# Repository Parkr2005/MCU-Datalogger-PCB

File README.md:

# MCU Data Logger PCB

A 4-layer PCB designed in KiCad for an ATmega328P-AU based microcontroller data logger. The board integrates a DS1337 real-time clock, dual 24LC1025 EEPROMs, ICSP programming interface, UART, I²C, and GPIO expansion headers.

## Features

- ATmega328P-AU Microcontroller
- DS1337 Real-Time Clock (RTC)
- Dual 24LC1025 EEPROMs
- 16 MHz System Crystal
- 32.768 kHz RTC Crystal
- ICSP Programming Header
- UART Header
- I²C Expansion Header
- GPIO Expansion Header
- Battery Input Header
- Status LEDs
- Four Mounting Holes
- Custom PCB Artwork

## PCB Specifications

| Parameter | Value |
|----------|-------|
| PCB CAD | KiCad |
| PCB Layers | 4 |
| MCU | ATmega328P-AU |
| RTC | DS1337 |
| EEPROM | 2 × 24LC1025 |
| Crystal | 16 MHz |
| RTC Crystal | 32.768 kHz |

## Project Structure

```text
├── README.md
├── .gitignore
├── MCU-Datalogger.kicad_pro
├── MCU-Datalogger.kicad_sch
└── MCU-Datalogger.kicad_pcb
```

## Verification

- ✅ Electrical Rules Check (ERC) Passed
- ✅ Design Rules Check (DRC) Passed
- ✅ Fully Routed PCB
- ✅ 3D PCB Model Generated

## Software Used

- KiCad

## Author

**Parthiv K R**

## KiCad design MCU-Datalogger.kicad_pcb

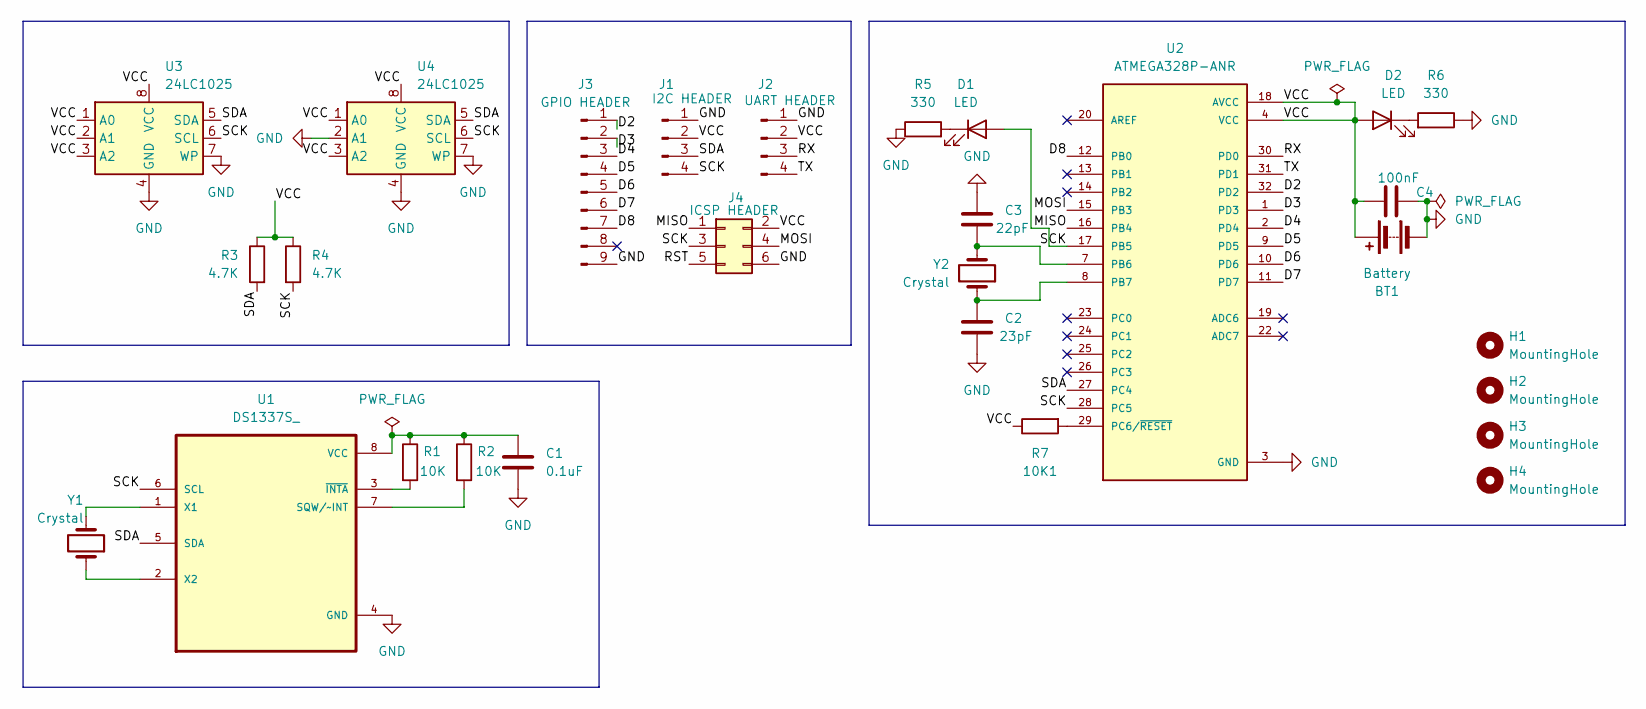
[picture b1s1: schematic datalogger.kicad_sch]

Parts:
10K1: R7; R_0805_2012Metric_Pad1.20x1.40mm_HandSolder
BT1: Battery; PinHeader_1x02_P2.54mm_Vertical
C1: 0.1uF; C_0805_2012Metric_Pad1.18x1.45mm_HandSolder
C2: 23pF; C_0805_2012Metric_Pad1.18x1.45mm_HandSolder
C3: 22pF; C_0805_2012Metric_Pad1.18x1.45mm_HandSolder
C4: 100nF; C_0805_2012Metric_Pad1.18x1.45mm_HandSolder
D1, D2: LED; LED_0805_2012Metric
H1, H2, H3, H4: MountingHole; MountingHole_2.1mm
J1: I2C HEADER; PinHeader_1x04_P2.54mm_Vertical
J2: UART HEADER; PinHeader_1x04_P2.54mm_Vertical
J3: GPIO HEADER; PinHeader_1x09_P2.54mm_Vertical
J4: ICSP HEADER; PinHeader_2x03_P2.54mm_Vertical
R1, R2: 10K; R_0805_2012Metric_Pad1.20x1.40mm_HandSolder
R3, R4: 4.7K; R_0805_2012Metric_Pad1.20x1.40mm_HandSolder
R5, R6: 330; R_0805_2012Metric_Pad1.20x1.40mm_HandSolder
U1: DS1337S_; SOIC127P600X175-8N
U2: ATMEGA328P-ANR; QFP80P900X900X120-32N
U3, U4: 24LC1025; SOIC-8_5.3x5.3mm_P1.27mm
Y1, Y2: Crystal; Crystal_SMD_5032-2Pin_5.0x3.2mm_HandSoldering

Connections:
/D2: J3.1, U2.32 (PD2)
/D3: J3.2, U2.1 (PD3)
/D4: J3.3, U2.2 (PD4)
/D5: J3.4, U2.9 (PD5)
/D6: J3.5, U2.10 (PD6)
/D7: J3.6, U2.11 (PD7)
/D8: J3.7, U2.12 (PB0)
/MISO: J4.1, U2.16 (PB4)
/MOSI: J4.4, U2.15 (PB3)
/RST: J4.5
/RX: J2.3, U2.30 (PD0)
/SCK: D1.2 (A), J1.4, J4.3, R4.2, U1.6 (SCL), U2.17 (PB5), U2.28 (PC5), U3.6 (SCL), U4.6 (SCL)
/SDA: J1.3, R3.2, U1.5 (SDA), U2.27 (PC4), U3.5 (SDA), U4.5 (SDA)
/TX: J2.4, U2.31 (PD1)
GND: BT1.2 (-), C1.2, C2.2, C3.1, C4.2, J1.1, J2.1, J3.9, J4.6, R5.1, R6.1, U1.4 (GND), U2.3 (GND), U2.5 (GND), U2.21 (GND), U3.4 (GND), U3.7 (WP), U4.2 (A1), U4.4 (GND), U4.7 (WP)
unnamed: D1.1 (K), R5.2
unnamed: D2.1 (K), R6.2
unnamed: R2.2, U1.7 (SQW/~INT)
unnamed: C1.1, R1.1, R2.1, U1.8 (VCC)
unnamed: U1.1 (X1), Y1.2
unnamed: U1.2 (X2), Y1.1
unnamed: R1.2, U1.3 (~INTA)
unnamed: C3.2, U2.7 (PB6), Y2.2
unnamed: C2.1, U2.8 (PB7), Y2.1
unnamed: 10K1.2, U2.29 (PC6/~RESET)
VCC: 10K1.1, BT1.1 (+), C4.1, D2.2 (A), J1.2, J2.2, J4.2, R3.1, R4.1, U2.4 (VCC), U2.6 (VCC), U2.18 (AVCC), U3.1 (A0), U3.2 (A1), U3.3 (A2), U3.8 (VCC), U4.1 (A0), U4.3 (A2), U4.8 (VCC)

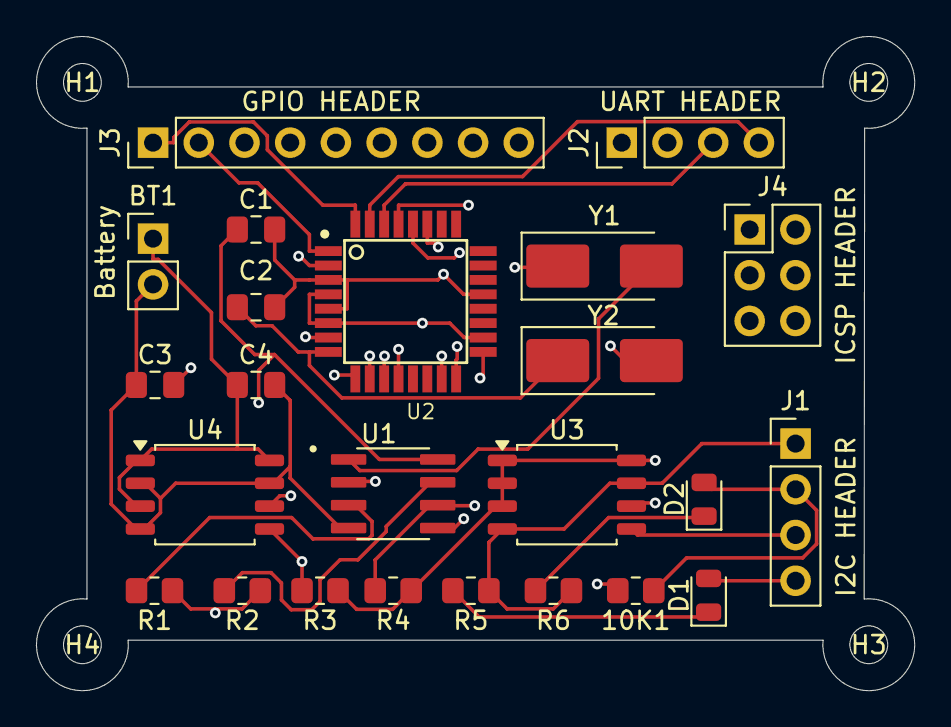
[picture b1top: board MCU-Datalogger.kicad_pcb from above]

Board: 4 copper layers, 48.8 x 36.3 mm, 28 parts (0 on the bottom side), 25 nets.

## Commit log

2026-06-29 Revise README for MCU Data Logger PCB
    Updated project description, added features, specifications, and verification details.
2026-06-29 Rename datalogger.kicad_pcb to MCU-Datalogger.kicad_pcb
2026-06-29 Rename datalogger.kicad_sch to MCU-Datalogger.kicad_sch
2026-06-29 Rename datalogger.kicad_pro to MCU-Datalogger.kicad_pro
